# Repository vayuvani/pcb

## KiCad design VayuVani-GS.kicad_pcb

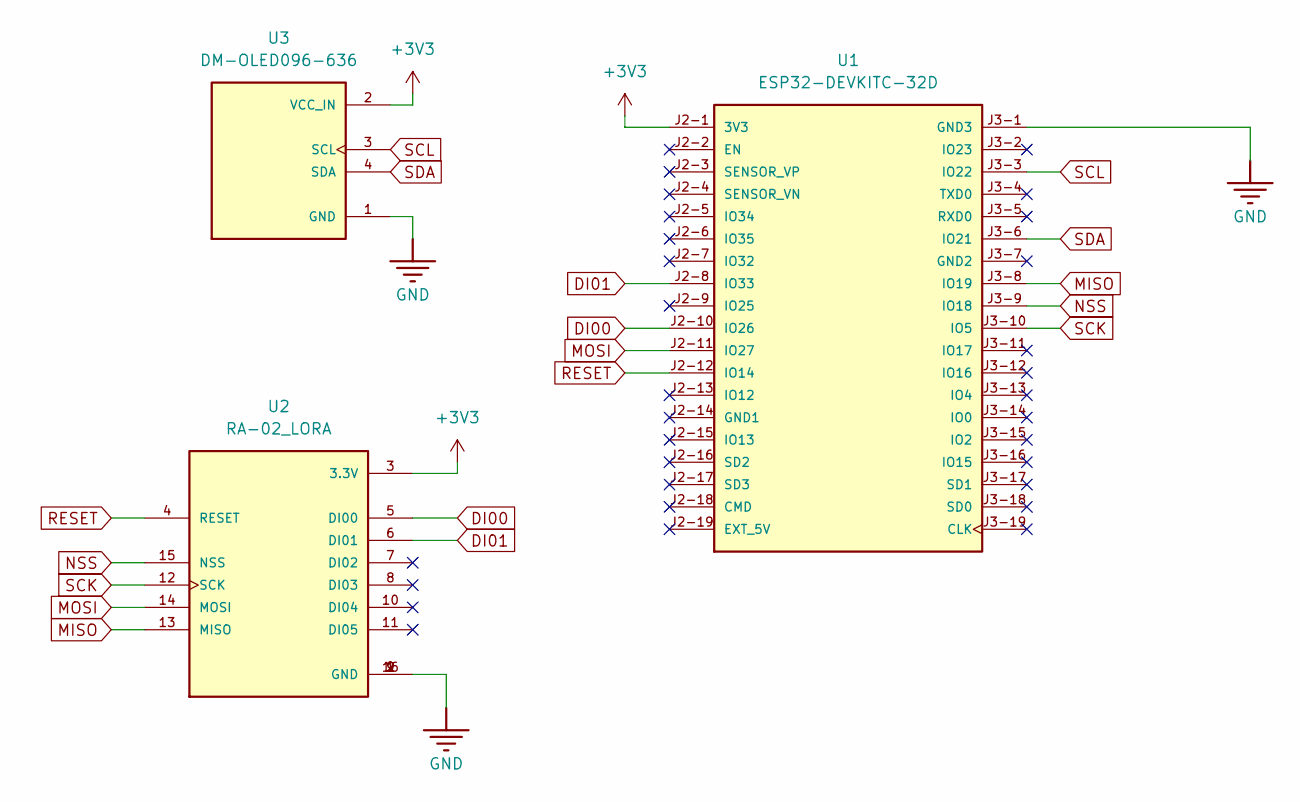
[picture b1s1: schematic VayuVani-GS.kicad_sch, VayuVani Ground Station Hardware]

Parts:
U1: ESP32-DEVKITC-32D; MODULE_ESP32-DEVKITC-32D; PARTREV V4
U2: RA-02_LORA; lora V2; PARTREV 2018/03/02
U3: DM-OLED096-636; MODULE_DM-OLED096-636; PARTREV 2018-09-10

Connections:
+3V3: U1.J2-1 (3V3), U2.3 (3.3V), U3.2 (VCC_IN)
DI00: U1.J2-10 (IO26), U2.5 (DI00)
DI01: U1.J2-8 (IO33), U2.6 (DI01)
GND: U1.J3-1 (GND3), U2.1 (GND), U2.2 (GND), U2.9 (GND), U2.16 (GND), U3.1 (GND)
MISO: U1.J3-8 (IO19), U2.13 (MISO)
MOSI: U1.J2-11 (IO27), U2.14 (MOSI)
NSS: U1.J3-9 (IO18), U2.15 (NSS)
RESET: U1.J2-12 (IO14), U2.4 (RESET)
SCK: U1.J3-10 (IO5), U2.12 (SCK)
SCL: U1.J3-3 (IO22), U3.3 (SCL)
SDA: U1.J3-6 (IO21), U3.4 (SDA)

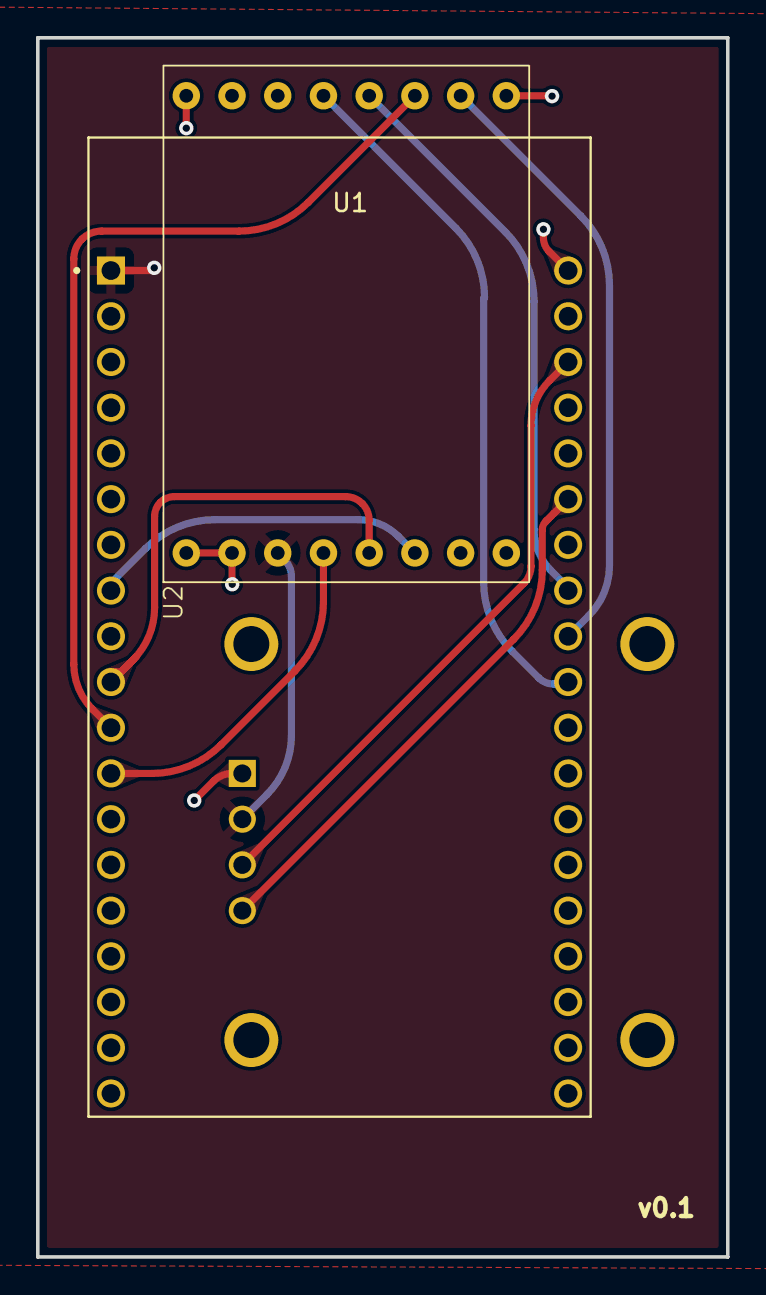
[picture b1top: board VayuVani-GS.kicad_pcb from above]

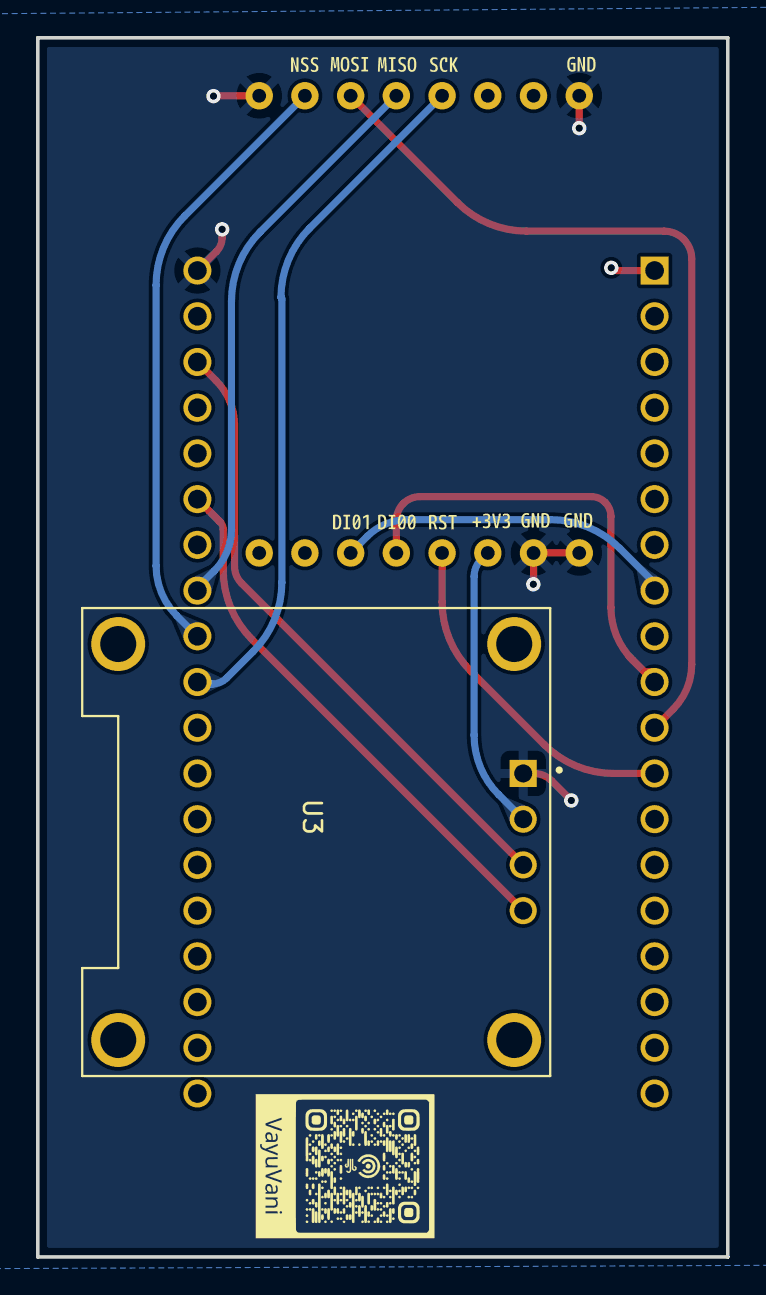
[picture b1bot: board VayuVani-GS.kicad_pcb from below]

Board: 2 copper layers, 38.3 x 67.7 mm, 14 parts (12 on the bottom side), 11 nets.

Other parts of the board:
kibuzzard-6717FCAE: G***; kibuzzard-6717FCAE
kibuzzard-67193F1F: G***; kibuzzard-67193F1F
kibuzzard-67193F4E: G***; kibuzzard-67193F4E
kibuzzard-67193F6C: G***; kibuzzard-67193F6C
kibuzzard-67193F40: G***; kibuzzard-67193F40
kibuzzard-67193FAE, kibuzzard-67193FAE#2: G***; kibuzzard-67193FAE
kibuzzard-67193FCE: G***; kibuzzard-67193FCE
kibuzzard-67193FDF: G***; kibuzzard-67193FDF
kibuzzard-67193FFA: G***; kibuzzard-67193FFA
kibuzzard-67194008: G***; kibuzzard-67194008

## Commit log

2024-11-25 Add: v0.1
